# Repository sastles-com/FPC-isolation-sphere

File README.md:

# Isolation Sphere V2

直径 100 mm の球体 LED ディスプレイ。約 800 個の WS2812-2020 を  
**ゴールドバーグ多面体 T=81** の球面に配置した "デジタル地球儀" 風ピクセルディスプレイ。

**A 100 mm spherical LED display with ~800 WS2812-2020 pixels  
arranged on a Goldberg polyhedron (T=81) shell.**

---

## コンセプト / Concept

前作はスパイラル配線＋接着剤固定で LED 1 個の故障が全損につながる設計だった。  
V2 では **カセット交換式・接着剤ゼロ** に全面刷新する。

> V1 was glued together — a single dead LED bricked the sphere.  
> V2 makes every section a **hot-swappable cassette with zero adhesive**.

| 項目 | 仕様 |
|---|---|
| 外径 | φ100 mm |
| 多面体 | Goldberg G(9,0)、T=81 |
| LED | WS2812-2020 × **800 個** |
| 分割 | 経度 5 × 南北 2 = **10 カセット** |
| コントローラ | ESP32 系（6 並列 RMT/PIO 出力） |
| バッテリ | LiPo 2000 mAh × 2 |

---

## 現在のフェーズ / Current Phase

**概念設計 + 3D CAD スクリプト開発中**

- [x] Goldberg T=81 メッシュ生成（`goldberg.py`）
- [x] カセット分割・可視化（Blender Python）
- [x] ヘキサゴン錐 + 円柱アパーチャの Boolean 生成（`aperture_boolean_demo.py`）
- [ ] カセット外殻 STL 完成
- [ ] FPC（骨組み基板）KiCad 設計
- [ ] 極専用 Rigid PCB × 2
- [ ] 赤道マザーリング基板
- [ ] ファームウェア（ESP32）

---

## 3D ビューア / 3D Viewer

生成した STL を Lolipop サーバーで公開中：

| モデル | URL |
|---|---|
| 全球アパーチャ | http://tajmahal.mond.jp/isolation-sphere/web/output/aperture_demo_fullsphere_viewer.html |
| カセット 0 のみ | http://tajmahal.mond.jp/isolation-sphere/web/output/aperture_demo_cassette0_viewer.html |
| ヘキサゴン錐（面取りあり） | http://tajmahal.mond.jp/isolation-sphere/web/output/hex_pyramids_l5_b0.5_viewer.html |

---

## セットアップ / Setup

```bash
# Python 3.11 + uv が必要
uv sync
```

---

## スクリプト一覧 / Scripts

### `shell-cad/scripts/goldberg.py`
Goldberg G(m,0) 多面体ジェネレータ。T=81 メッシュを OBJ で出力。

```bash
uv run python shell-cad/scripts/goldberg.py        # T=81, r=50mm
uv run python shell-cad/scripts/goldberg.py -m 3   # T=9
```

### `shell-cad/scripts/hex_pyramids.py`
各ヘキサゴン面から LED アパーチャ用の六角錐を生成。OBJ / STL 出力。

```bash
uv run python shell-cad/scripts/hex_pyramids.py --l_h 5 --bevel 0.5 --base_r 52
```

| パラメータ | 説明 |
|---|---|
| `--l_h` | 錐の深さ mm |
| `--bevel` | 辺の面取り mm（0=シャープ） |
| `--base_r` | 底面を配置する半径 mm |

### `shell-cad/scripts/aperture_boolean_demo.py`
球殻から六角錐 + 円柱ボアを Boolean 差分で除去した STL を生成。  
スクリプト先頭のパラメータブロックで形状をチューニングできる。

```bash
uv run python shell-cad/scripts/aperture_boolean_demo.py            # 全球
uv run python shell-cad/scripts/aperture_boolean_demo.py --cassette 0  # 1カセットのみ
```

**チューニングパラメータ（スクリプト先頭）:**

```python
R_OUTER     = 52.0   # 外殻半径 mm
R_INNER     = 47.0   # 内殻半径 mm  (差 = 壁厚)
L_H         =  8.0   # 錐の深さ mm
BEVEL       =  0.0   # 面取り mm
CYL_R       =  1.2   # ボア半径 mm
CYL_ENABLE  = True   # False で円柱を無効化
SPHERE_SUBS =  5     # 球メッシュ細分割数
CYL_SECTS   = 16     # 円柱多角形分割数
```

### `shell-cad/scripts/generate_stl_viewer.py`
STL → Three.js インタラクティブ HTML ビューアを生成。

```bash
uv run python shell-cad/scripts/generate_stl_viewer.py shell-cad/output/foo.stl
```

### `shell-cad/scripts/upload_to_lolipop.sh`
`web/output/` 以下を Lolipop FTP サーバーへアップロード。  
認証情報は `.ftp_credentials`（gitignore 済）に記載。

```bash
bash shell-cad/scripts/upload_to_lolipop.sh           # 一括
bash shell-cad/scripts/upload_to_lolipop.sh path/to/file.html  # 単ファイル
```

---

## フォルダ構成 / Repository Layout

```text
.
├── CLAUDE.md                    Claude Code 用プロジェクトガイド
├── docs/
│   ├── 10pieces-isolation-sphere-concept.md  設計議論ログ（一次資料）
│   ├── 01-shell-cad.md          外殻 CAD 仕様
│   ├── 02-fpc-kicad.md          FPC / Rigid PCB 仕様
│   └── 03-power-charging.md     電源・充電仕様
├── shell-cad/
│   └── scripts/                 Python 生成スクリプト群
├── fpc-kicad/
│   └── legacy/                  V1 KiCad スクリプト（参照用）
├── shared/                      Blender ↔ KiCad 共有データ（LED座標 CSV）
└── web/output/                  生成 HTML + STL（gitignore）
```

---

## ライセンス / License

Private repository — Yasuo Katano

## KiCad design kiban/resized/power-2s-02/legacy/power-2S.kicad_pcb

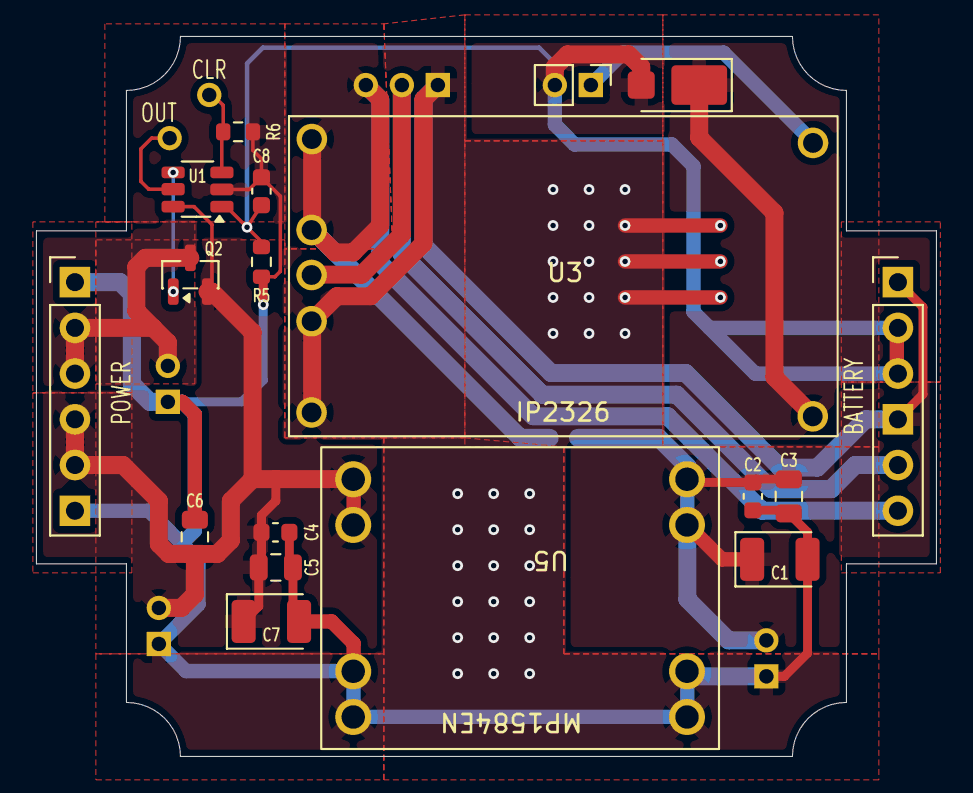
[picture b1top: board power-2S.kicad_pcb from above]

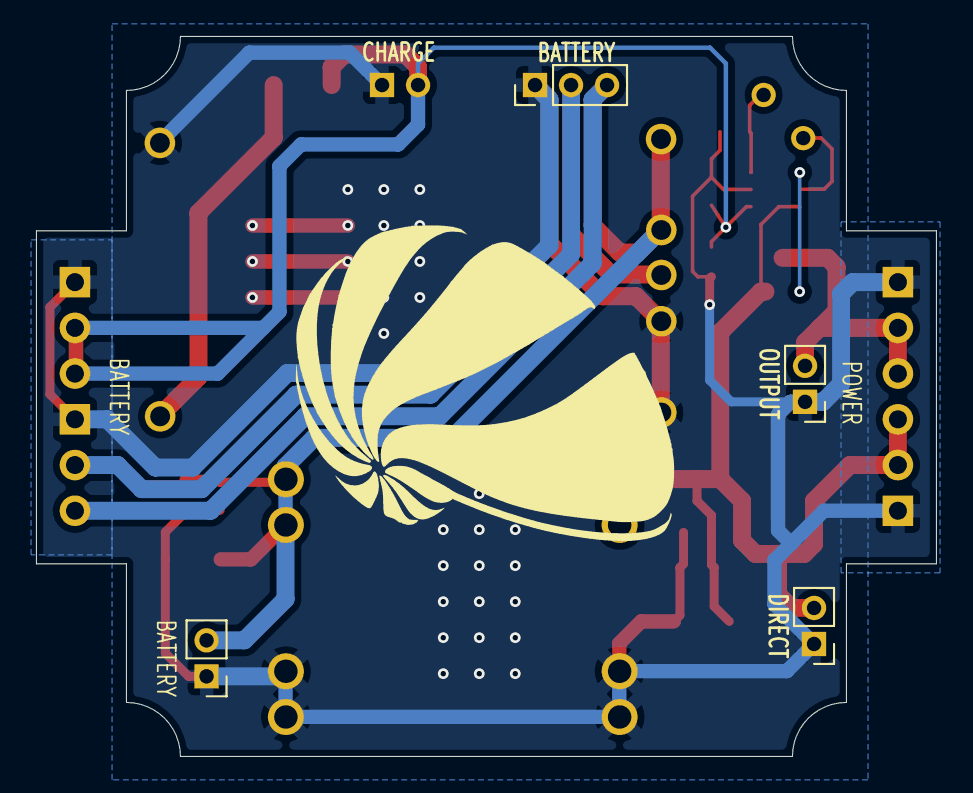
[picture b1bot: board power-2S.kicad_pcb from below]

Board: 2 copper layers, 50.0 x 40.0 mm, 25 parts (5 on the bottom side), 11 nets.

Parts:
C1, C7: 100uF; CP_EIA-3528-12_Kemet-T
C2, C4, C8: 0.1uF; C_0603_1608Metric
C3, C5, C6: 22uF; C_0805_2012Metric
D1: D_Schottky_Small; Vishay_SMPA
FB1: FerriteBead; L_0603_1608Metric
J1: BATTERY; PinHeader_1x03_P2.00mm_Vertical
J3: BATTERY; PinHeader_1x02_P2.00mm_Vertical
J4: DIRECT; PinHeader_1x02_P2.00mm_Vertical
J7: VOUT; PinHeader_1x06_P2.54mm_Vertical
J8: VIN; PinHeader_1x06_P2.54mm_Vertical
J9: OUTPUT; PinHeader_1x02_P2.00mm_Vertical
J11: OUT; PinHeader_1x01_P2.00mm_Vertical
J12: CLR; PinHeader_1x01_P2.00mm_Vertical
J14: CHARGE; PinHeader_1x02_P2.00mm_Vertical
Q2: DMG3415; SOT-23
R5: 47kΩ; R_0603_1608Metric
R6: 10kΩ; R_0603_1608Metric
U1: MAX16054; TSOT-23-6_HandSoldering
U3: IP2326; TS2326
U5: MP1584EN

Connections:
BM: J1.2, J8.5, U3.2 (BM)
CHARGE: D1.1 (K), U3.4 (VIN)
CLR: J12.1 (Pin_1_1), R6.2, U1.3 (CLR)
GATE: Q2.1 (G), U1.4 (OUT_)
OUT: J11.1 (Pin_1_1), U1.5 (OUT)
P+: FB1.1, J1.3, J8.6, U3.1 (B+)
PGND: C1.2, C2.2, C3.2, C4.2, C5.2, C6.2, C7.2, C8.2, J1.1, J3.1, J4.1, J7.1, J7.6, J8.1, J8.4, J9.1, J14.1, R5.2, R6.1, U1.2 (GND), U3.3 (B-), U3.5 (GND), U5.1 (IN-), U5.4 (OUT-)
POWER: C8.1, D1.2 (A), J8.2, J8.3, J14.2, R5.1, U1.1 (IN)
VIN: C1.1, C2.1, C3.1, FB1.2, J3.2, U5.2 (IN+)
VOUT: C4.1, C5.1, C6.1, C7.1, J4.2, J7.4, J7.5, Q2.2 (S), U1.6 (VCC), U5.3 (OUT+)
VOUT_SWITCHED: J7.2, J7.3, J9.2, Q2.3 (D)

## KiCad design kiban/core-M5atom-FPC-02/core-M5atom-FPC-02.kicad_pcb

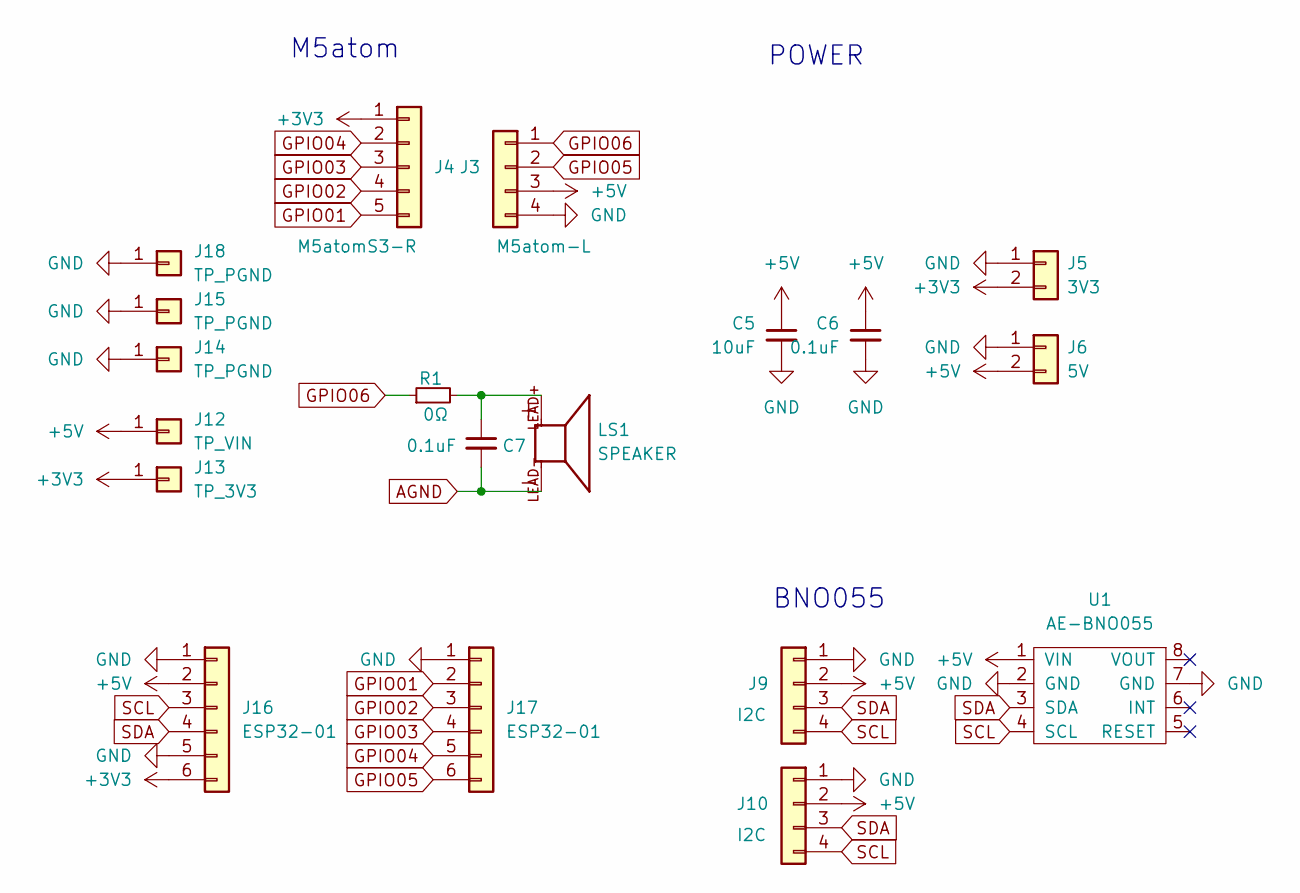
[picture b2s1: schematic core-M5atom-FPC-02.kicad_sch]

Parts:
C5: 10uF; C_0603_1608Metric_Pad1.08x0.95mm_HandSolder
C6, C7: 0.1uF; C_0603_1608Metric_Pad1.08x0.95mm_HandSolder
J3: M5atom-L; PinHeader_1x04_P2.54mm_Vertical_SMD_Pin1Left
J4: M5atomS3-R; PinHeader_1x05_P2.54mm_Vertical_SMD_Pin1Left
J5: 3V3; PinHeader_1x02_P2.00mm_Vertical
J6: 5V; PinHeader_1x02_P2.00mm_Vertical
J9, J10: I2C; PinHeader_1x04_P2.00mm_Vertical
J12: TP_VIN; PinHeader_1x01_P2.54mm_Vertical
J13: TP_3V3; PinHeader_1x01_P2.54mm_Vertical
J14, J15, J18: TP_PGND; PinHeader_1x01_P2.54mm_Vertical
J16, J17: ESP32-01; PinHeader_1x06_P2.54mm_Vertical
LS1: SPEAKER; speaker-PKLCS1212; PARTREV C
R1: 0Ω; C_0603_1608Metric
U1: AE-BNO055; AE-BNO055-nohole

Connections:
+3V3: J4.1, J5.2, J13.1 (Pin_1_1), J16.6
+5V: C5.1, C6.1, J3.3, J6.2, J9.2, J10.2, J12.1 (Pin_1_1), J16.2, U1.1 (VIN)
AGND: C7.2, LS1.LEAD-
GND: C5.2, C6.2, J3.4, J5.1, J6.1, J9.1, J10.1, J14.1 (Pin_1_1), J15.1 (Pin_1_1), J16.1, J16.5, J17.1, J18.1 (Pin_1_1), U1.2 (GND), U1.7 (GND)
GPIO01: J4.5, J17.2
GPIO02: J4.4, J17.3
GPIO03: J4.3, J17.4
GPIO04: J4.2, J17.5
GPIO05: J3.2, J17.6
GPIO06: J3.1, R1.1
unnamed: C7.1, LS1.LEAD+, R1.2
SCL: J9.4, J10.4, J16.3, U1.4 (SCL)
SDA: J9.3, J10.3, J16.4, U1.3 (SDA)

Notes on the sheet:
M5atom
BNO055
POWER

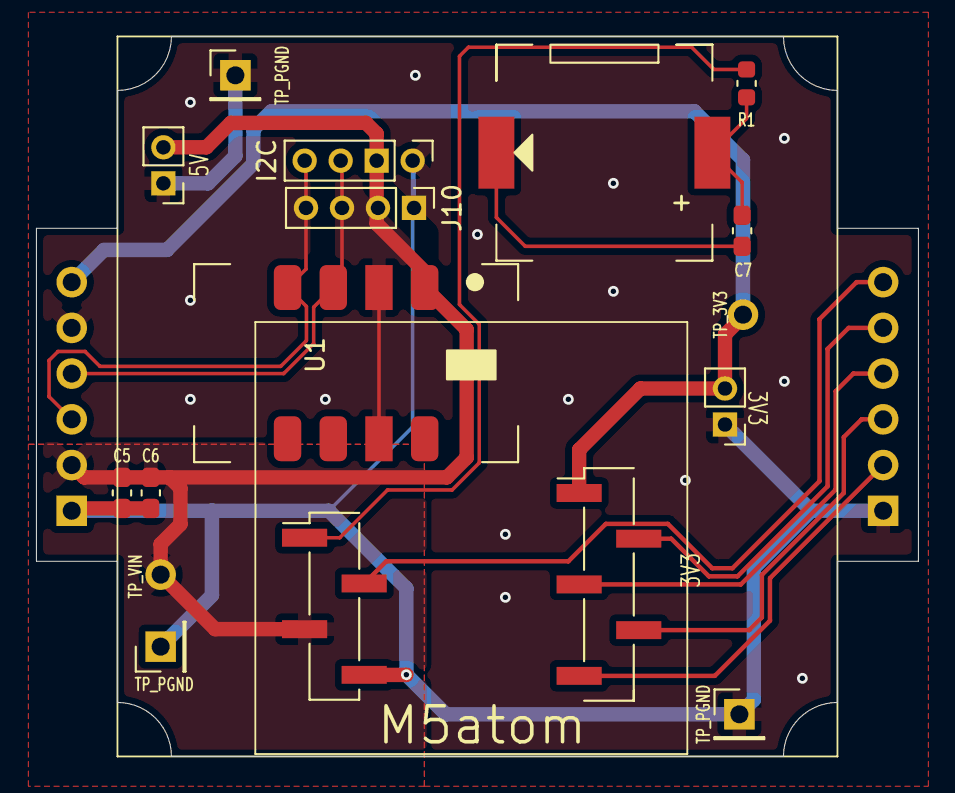
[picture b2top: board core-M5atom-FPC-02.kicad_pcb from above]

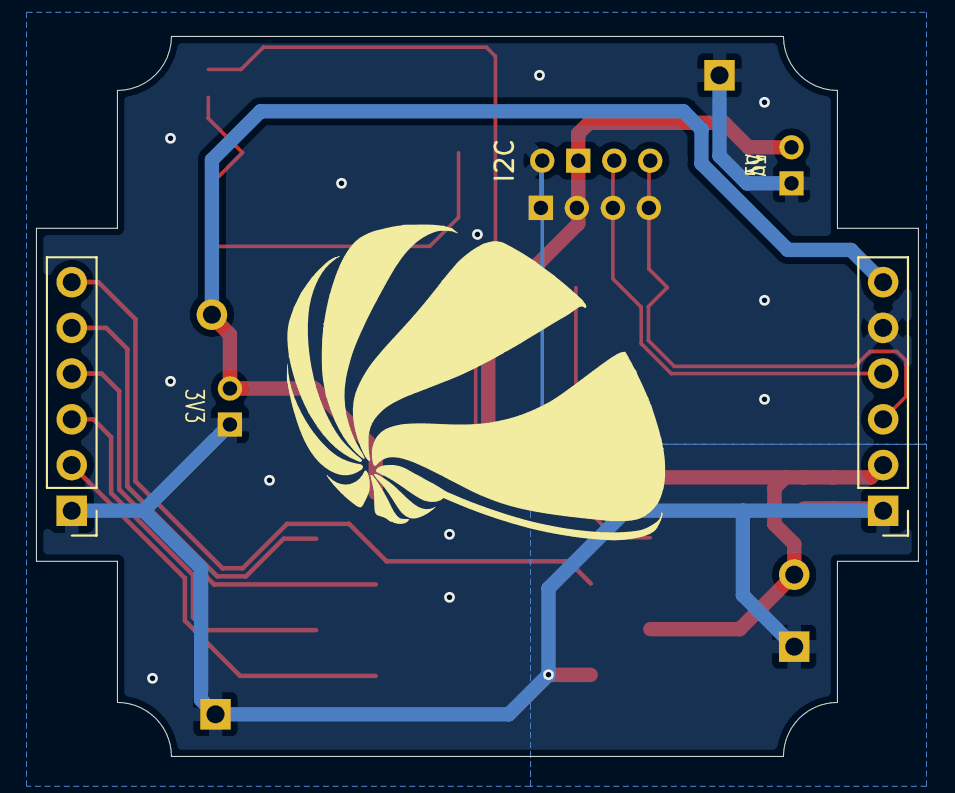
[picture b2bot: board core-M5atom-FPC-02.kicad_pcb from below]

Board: 2 copper layers, 49.0 x 40.0 mm, 19 parts (2 on the bottom side), 13 nets.

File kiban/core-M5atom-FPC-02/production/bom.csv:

Designator,Footprint,Quantity,Value,LCSC Part #
C5,0603,1,10uF,
"C6, C7",0603,2,0.1uF,
J12,PinHeader_1x01_P2.54mm_Vertical,1,TP_VIN,
J13,PinHeader_1x01_P2.54mm_Vertical,1,TP_3V3,
"J14, J15, J18",PinHeader_1x01_P2.54mm_Vertical,3,TP_PGND,
"J16, J17",PinHeader_1x06_P2.54mm_Vertical,2,ESP32-01,
J3,PinHeader_1x04_P2.54mm_Vertical_SMD_Pin1Left,1,M5atom-L,
J4,PinHeader_1x05_P2.54mm_Vertical_SMD_Pin1Left,1,M5atomS3-R,
J5,PinHeader_1x02_P2.00mm_Vertical,1,3V3,
J6,PinHeader_1x02_P2.00mm_Vertical,1,5V,
J9,PinHeader_1x04_P2.00mm_Vertical,1,I2C,
LS1,speaker-PKLCS1212,1,SPEAKER,
R1,0603,1,0Ω,
U1,AE-BNO055-nohole,1,AE-BNO055,

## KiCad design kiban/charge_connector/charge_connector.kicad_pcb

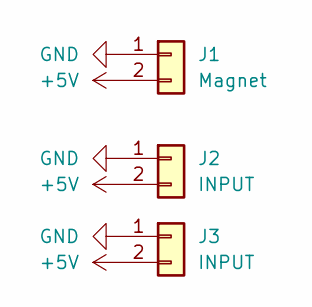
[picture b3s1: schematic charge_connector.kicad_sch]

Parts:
J1: Magnet; magnet_contact
J2: INPUT; PinHeader_1x02_P2.00mm_Vertical
J3: INPUT; PinHeader_1x02_P2.54mm_Vertical

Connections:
+5V: J1.2, J2.2, J3.2
GND: J1.1, J2.1, J3.1

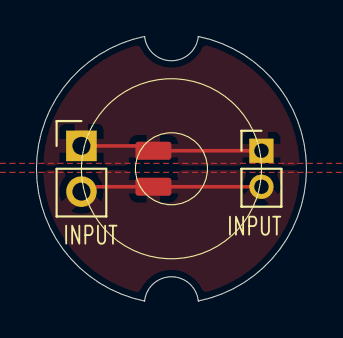
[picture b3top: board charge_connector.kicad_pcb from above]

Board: 2 copper layers, 15.0 x 14.7 mm, 3 parts (0 on the bottom side), 2 nets.

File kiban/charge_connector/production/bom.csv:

Designator,Footprint,Quantity,Value,LCSC Part #
J1,magnet_contact,1,Magnet,
J2,PinHeader_1x02_P2.00mm_Vertical,1,INPUT,
J3,PinHeader_1x02_P2.54mm_Vertical,1,INPUT,

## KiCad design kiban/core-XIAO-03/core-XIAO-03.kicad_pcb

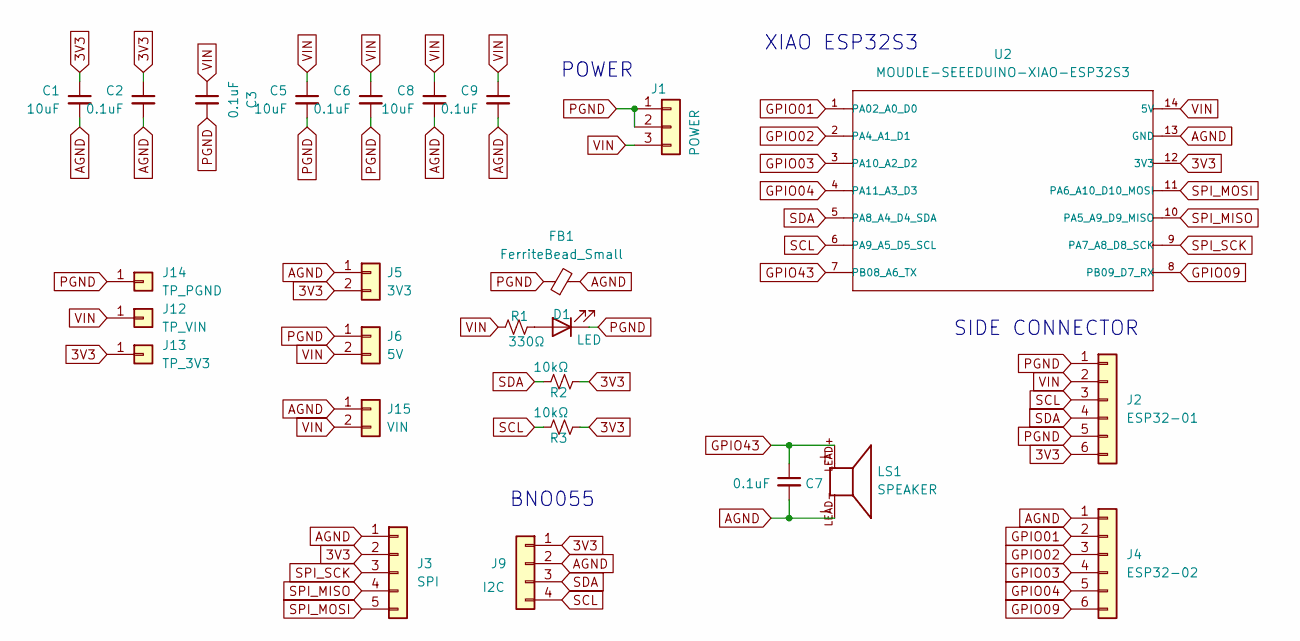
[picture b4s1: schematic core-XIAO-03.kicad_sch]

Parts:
C1, C5, C8: 10uF; C_0603_1608Metric_Pad1.08x0.95mm_HandSolder
C2, C3, C6, C7, C9: 0.1uF; C_0603_1608Metric_Pad1.08x0.95mm_HandSolder
D1: LED; LED_0603_1608Metric
FB1: FerriteBead_Small; C_0603_1608Metric_Pad1.08x0.95mm_HandSolder
J1: POWER; PinHeader_1x03_P2.00mm_Vertical
J2: ESP32-01; PinHeader_1x06_P2.54mm_Vertical
J3: SPI; PinHeader_1x05_P2.00mm_Vertical
J4: ESP32-02; PinHeader_1x06_P2.54mm_Vertical
J5: 3V3; PinHeader_1x02_P2.00mm_Vertical
J6: 5V; PinHeader_1x02_P2.00mm_Vertical
J9: I2C; PinHeader_1x04_P2.54mm_Vertical
J12: TP_VIN; PinHeader_1x01_P2.54mm_Vertical
J13: TP_3V3; PinHeader_1x01_P2.54mm_Vertical
J14: TP_PGND; PinHeader_1x01_P2.54mm_Vertical
J15: VIN; PinHeader_1x02_P2.00mm_Vertical
LS1: SPEAKER; speaker-PKLCS1212; PARTREV C
R1: 330Ω; R_0603_1608Metric
R2, R3: 10kΩ; R_0603_1608Metric
U2: MOUDLE-SEEEDUINO-XIAO-ESP32S3; XIAO-RP2350

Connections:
3V3: C1.1, C2.1, J2.6, J3.2, J5.2, J9.1, J13.1 (Pin_1_1), R2.1, R3.1, U2.12 (3V3)
AGND: C1.2, C2.2, C7.2, C8.2, C9.2, FB1.2, J3.1, J4.1, J5.1, J9.2, J15.1, LS1.LEAD-, U2.13 (GND)
GPIO01: J4.2, U2.1 (PA02_A0_D0)
GPIO02: J4.3, U2.2 (PA4_A1_D1)
GPIO03: J4.4, U2.3 (PA10_A2_D2)
GPIO04: J4.5, U2.4 (PA11_A3_D3)
GPIO09: J4.6, U2.8 (PB09_D7_RX)
GPIO43: C7.1, LS1.LEAD+, U2.7 (PB08_A6_TX)
unnamed: D1.2 (A), R1.2
PGND: C3.2, C5.2, C6.2, D1.1 (K), FB1.1, J1.1, J1.2, J2.1, J2.5, J6.1, J14.1 (Pin_1_1); also elsewhere on the board
SCL: J2.3, J9.4, R3.2, U2.6 (PA9_A5_D5_SCL)
SDA: J2.4, J9.3, R2.2, U2.5 (PA8_A4_D4_SDA)
SPI_MISO: J3.4, U2.10 (PA5_A9_D9_MISO)
SPI_MOSI: J3.5, U2.11 (PA6_A10_D10_MOSI)
SPI_SCK: J3.3, U2.9 (PA7_A8_D8_SCK)
VIN: C3.1, C5.1, C6.1, C8.1, C9.1, J1.3, J2.2, J6.2, J12.1 (Pin_1_1), J15.2, R1.1, U2.14 (5V)

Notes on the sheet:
XIAO ESP32S3
SIDE CONNECTOR
BNO055
POWER

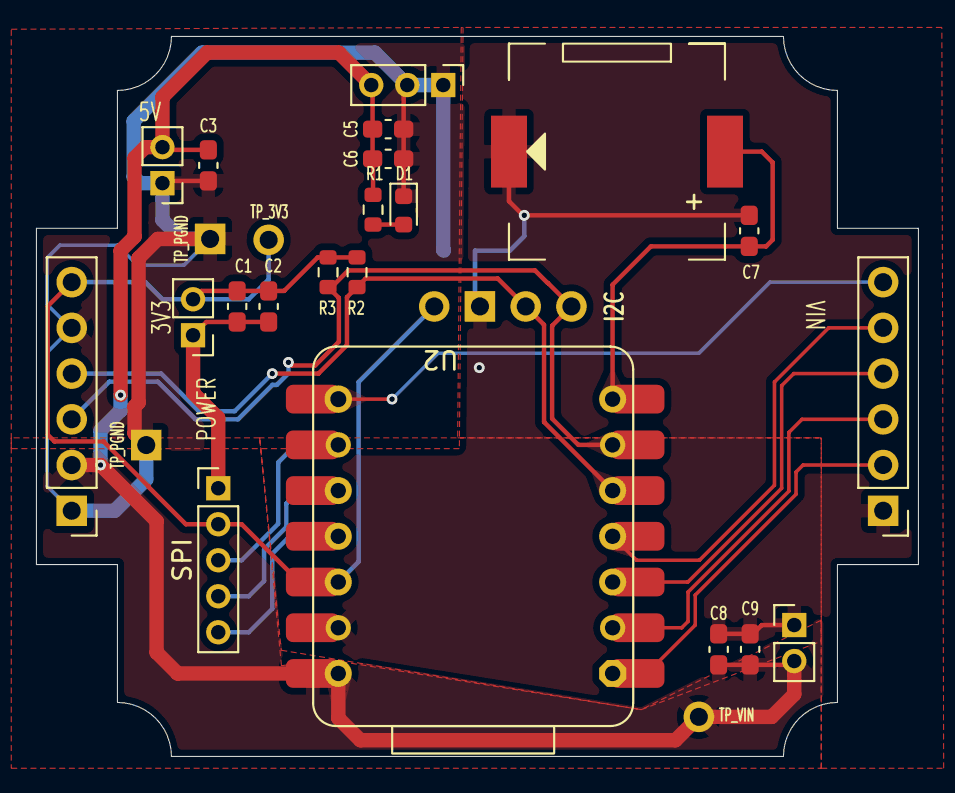
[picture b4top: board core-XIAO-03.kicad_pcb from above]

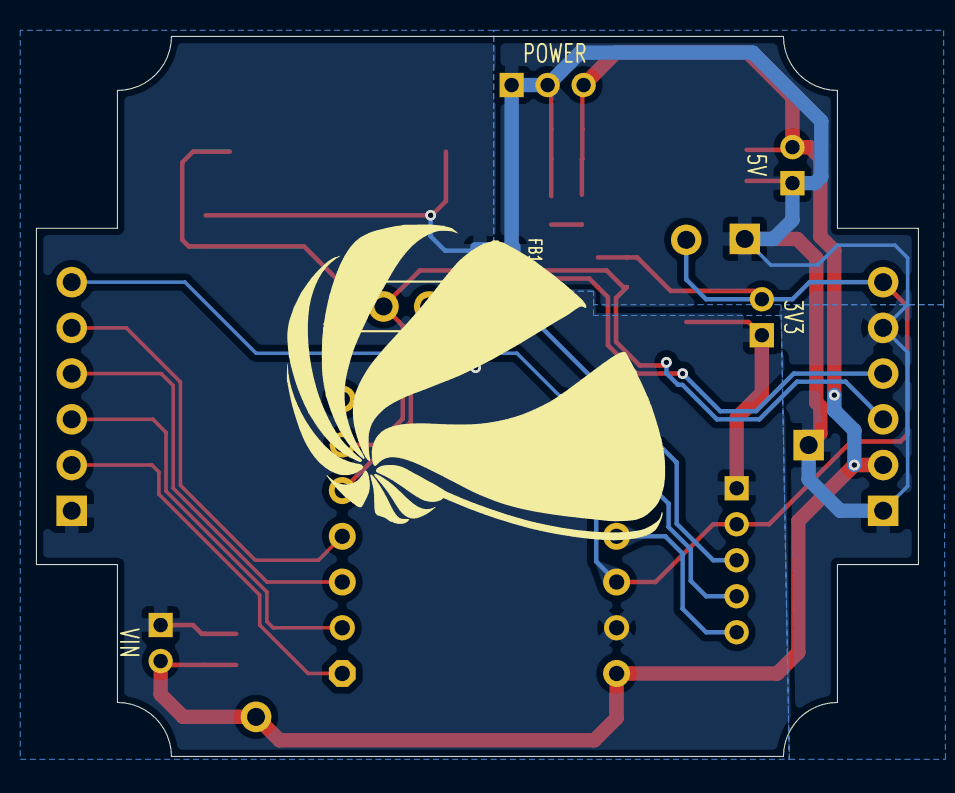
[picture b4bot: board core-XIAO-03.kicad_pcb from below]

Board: 2 copper layers, 49.0 x 40.0 mm, 27 parts (2 on the bottom side), 16 nets.

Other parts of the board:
J14#2: TP_PGND; PinHeader_1x01_P2.54mm_Vertical

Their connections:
PGND: J14#2.1 (Pin_1_1); also elsewhere on the board

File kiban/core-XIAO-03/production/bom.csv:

Designator,Footprint,Quantity,Value,LCSC Part #
"C1, C5, C8",0603,3,10uF,
"C2, C3, C6, C7, C9",0603,5,0.1uF,
D1,0603,1,LED,
FB1,0603,1,FerriteBead_Small,
J1,PinHeader_1x03_P2.00mm_Vertical,1,POWER,
J12,PinHeader_1x01_P2.54mm_Vertical,1,TP_VIN,
J13,PinHeader_1x01_P2.54mm_Vertical,1,TP_3V3,
"J14_2, J14",PinHeader_1x01_P2.54mm_Vertical,2,TP_PGND,
J15,PinHeader_1x02_P2.00mm_Vertical,1,VIN,
J2,PinHeader_1x06_P2.54mm_Vertical,1,ESP32-01,
J3,PinHeader_1x05_P2.00mm_Vertical,1,SPI,
J4,PinHeader_1x06_P2.54mm_Vertical,1,ESP32-02,
J5,PinHeader_1x02_P2.00mm_Vertical,1,3V3,
J6,PinHeader_1x02_P2.00mm_Vertical,1,5V,
J9,PinHeader_1x04_P2.54mm_Vertical,1,I2C,
LS1,speaker-PKLCS1212,1,SPEAKER,
R1,0603,1,330Ω,
"R2, R3",0603,2,10kΩ,
U2,XIAO-RP2350,1,MOUDLE-SEEEDUINO-XIAO-ESP32S3,

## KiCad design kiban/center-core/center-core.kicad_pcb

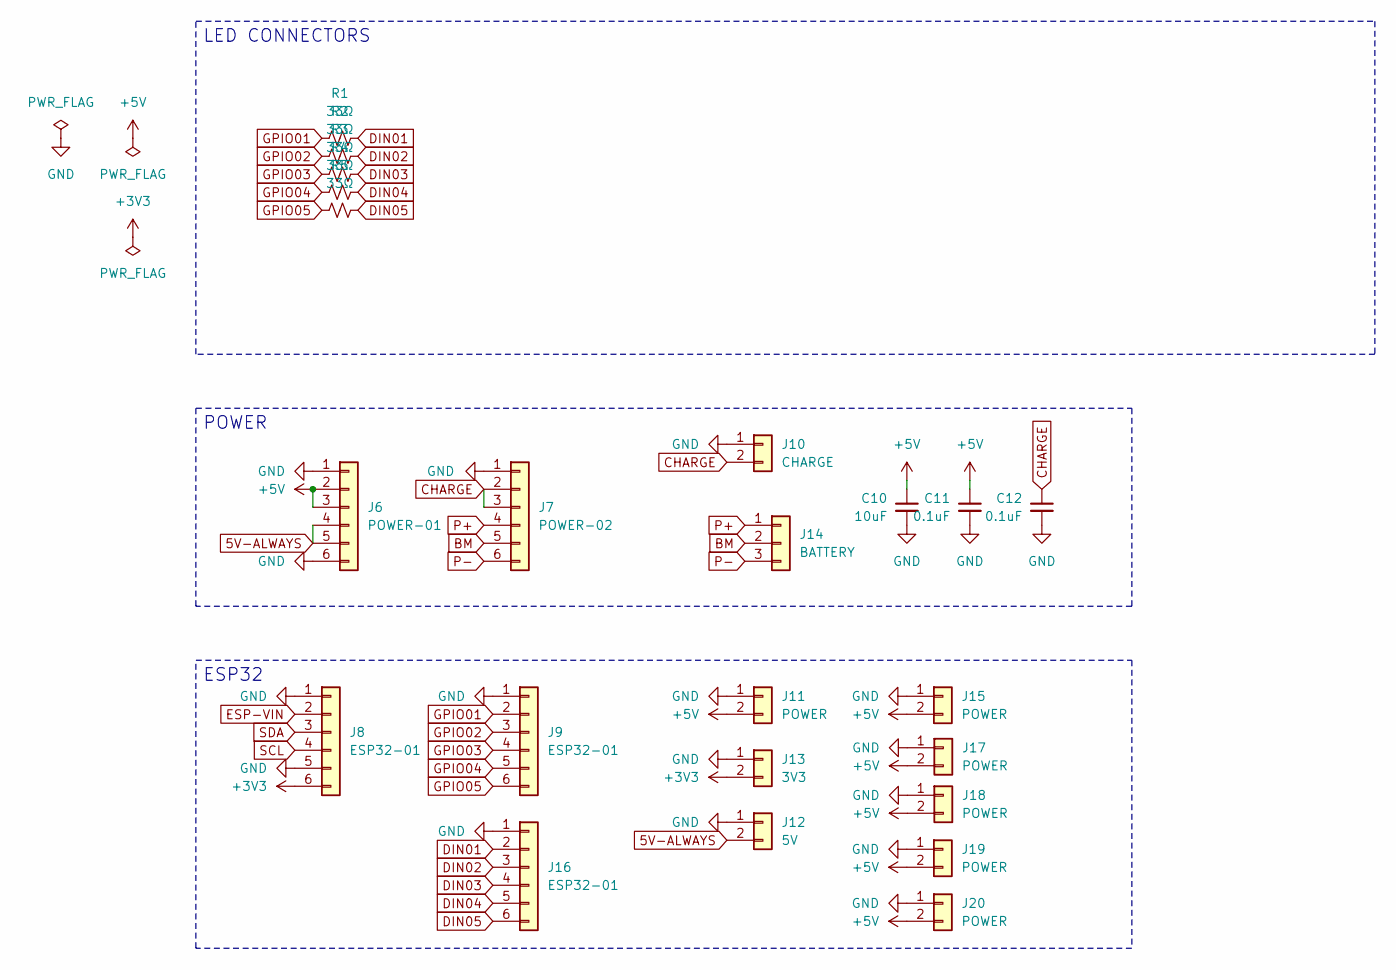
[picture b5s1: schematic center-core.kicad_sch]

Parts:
C10: 10uF; C_0603_1608Metric_Pad1.08x0.95mm_HandSolder
C11, C12: 0.1uF; C_0603_1608Metric_Pad1.08x0.95mm_HandSolder
J6: POWER-01; PinHeader_1x06_P2.54mm_Vertical
J7: POWER-02; PinHeader_1x06_P2.54mm_Vertical
J8, J9, J16: ESP32-01; PinHeader_1x06_P2.54mm_Vertical
J10: CHARGE; PinHeader_1x02_P2.00mm_Vertical
J11, J15, J17, J18, J19, J20: POWER; PinHeader_1x02_P2.00mm_Vertical
J12: 5V; PinHeader_1x02_P2.00mm_Vertical
J13: 3V3; PinHeader_1x02_P2.00mm_Vertical
J14: BATTERY; PinHeader_1x03_P2.00mm_Vertical
R1, R2, R3, R4, R5: 33Ω; R_0603_1608Metric

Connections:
5V-ALWAYS: J6.4, J6.5, J12.2
+3V3: J8.6, J13.2
+5V: C10.1, C11.1, J6.2, J6.3, J11.2, J15.2, J17.2, J18.2, J19.2, J20.2
BM: J7.5, J14.2
CHARGE: C12.1, J7.2, J7.3, J10.2
DIN01: J16.2, R1.2
DIN02: J16.3, R2.2
DIN03: J16.4, R3.2
DIN04: J16.5, R4.2
DIN05: J16.6, R5.2
ESP-VIN: J8.2
GND: C10.2, C11.2, C12.2, J6.1, J6.6, J7.1, J8.1, J8.5, J9.1, J10.1, J11.1, J12.1, J13.1, J15.1, J16.1, J17.1, J18.1, J19.1, J20.1
GPIO01: J9.2, R1.1
GPIO02: J9.3, R2.1
GPIO03: J9.4, R3.1
GPIO04: J9.5, R4.1
GPIO05: J9.6, R5.1
P+: J7.4, J14.1
P-: J7.6, J14.3
SCL: J8.4
SDA: J8.3

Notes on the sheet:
POWER
ESP32
LED CONNECTORS

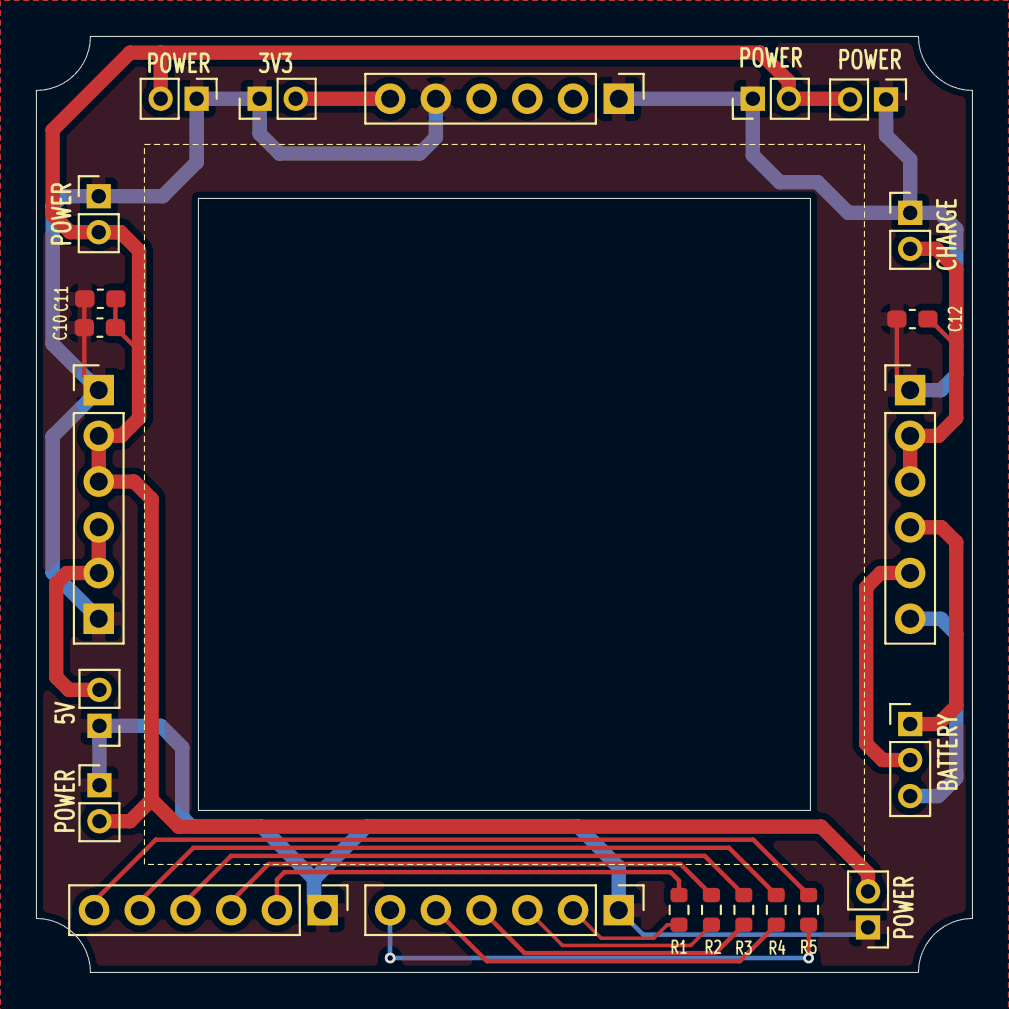
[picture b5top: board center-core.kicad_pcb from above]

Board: 2 copper layers, 52.0 x 52.0 mm, 23 parts (0 on the bottom side), 18 nets.

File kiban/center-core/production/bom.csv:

Designator,Footprint,Quantity,Value,LCSC Part #
C10,0603,1,10uF,
"C11, C12",0603,2,0.1uF,
J10,PinHeader_1x02_P2.00mm_Vertical,1,CHARGE,
"J11, J15, J17, J18, J19, J20",PinHeader_1x02_P2.00mm_Vertical,6,POWER,
J12,PinHeader_1x02_P2.00mm_Vertical,1,5V,
J13,PinHeader_1x02_P2.00mm_Vertical,1,3V3,
J14,PinHeader_1x03_P2.00mm_Vertical,1,BATTERY,
"J16, J8, J9",PinHeader_1x06_P2.54mm_Vertical,3,ESP32-01,
J6,PinHeader_1x06_P2.54mm_Vertical,1,POWER-01,
J7,PinHeader_1x06_P2.54mm_Vertical,1,POWER-02,
"R1, R2, R3, R4, R5",0603,5,33Ω,

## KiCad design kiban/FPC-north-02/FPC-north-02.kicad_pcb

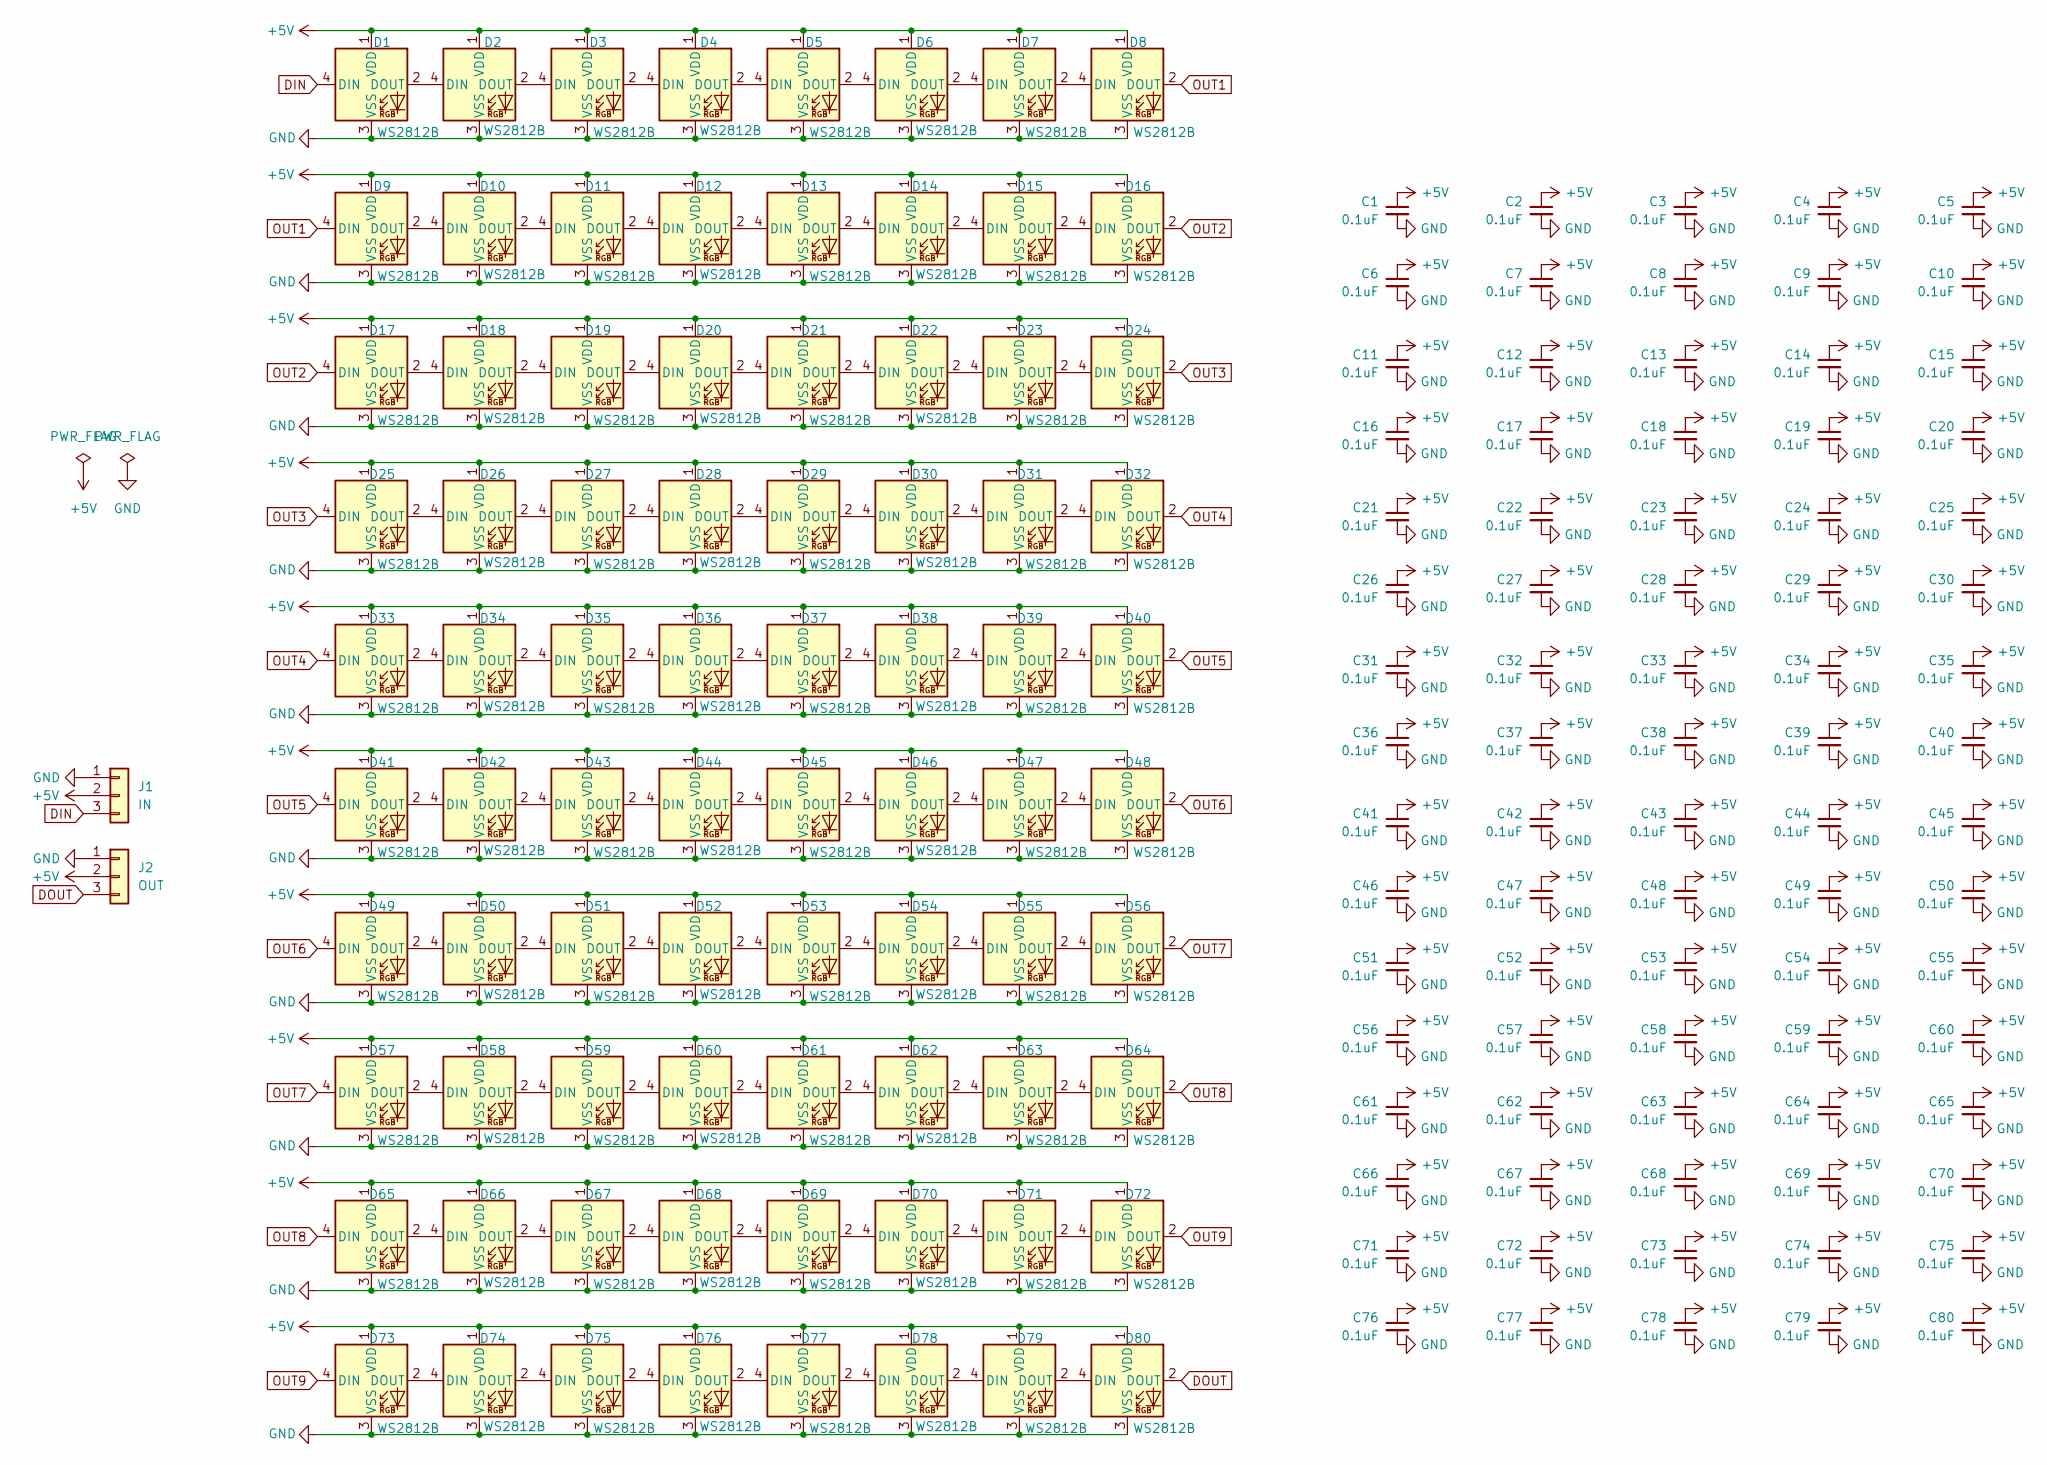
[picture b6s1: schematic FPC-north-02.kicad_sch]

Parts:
C1, C2, C3, C4, C5, C6, C7, C8, C9, C10, C11, C12, C13, C14, C15, C16, C17, C18, C19, C20, C21, C22, C23, C24, C25, C26, C27, C28, C29, C30, C31, C32, C33, C34, C35, C36, C37, C38, C39, C40, C41, C42, C43, C44, C45, C46, C47, C48, C49, C50, C51, C52, C53, C54, C55, C56, C57, C58, C59, C60, C61, C62, C63, C64, C65, C66, C67, C68, C69, C70, C71, C72, C73, C74, C75, C76, C77, C78, C79, C80: 0.1uF; C_0603_1608Metric
D1, D2, D3, D4, D5, D6, D7, D8, D9, D10, D11, D12, D13, D14, D15, D16, D17, D18, D19, D20, D21, D22, D23, D24, D25, D26, D27, D28, D29, D30, D31, D32, D33, D34, D35, D36, D37, D38, D39, D40, D41, D42, D43, D44, D45, D46, D47, D48, D49, D50, D51, D52, D53, D54, D55, D56, D57, D58, D59, D60, D61, D62, D63, D64, D65, D66, D67, D68, D69, D70, D71, D72, D73, D74, D75, D76, D77, D78, D79, D80: WS2812B; WS2812C-2020-nocut
J1: IN; PinHeader_1x03_P2.00mm_Vertical
J2: OUT; PinHeader_1x03_P2.00mm_Vertical

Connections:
+5V: C1.1, C2.1, C3.1, C4.1, C5.1, C6.1, C7.1, C8.1, C9.1, C10.1, C11.1, C12.1, C13.1, C14.1, C15.1, C16.1, C17.1, C18.1, C19.1, C20.1, C21.1, C22.1, C23.1, C24.1, C25.1, C26.1, C27.1, C28.1, C29.1, C30.1, C31.1, C32.1, C33.1, C34.1, C35.1, C36.1, C37.1, C38.1, C39.1, C40.1, C41.1, C42.1, C43.1, C44.1, C45.1, C46.1, C47.1, C48.1, C49.1, C50.1, C51.1, C52.1, C53.1, C54.1, C55.1, C56.1, C57.1, C58.1, C59.1, C60.1, C61.1, C62.1, C63.1, C64.1, C65.1, C66.1, C67.1, C68.1, C69.1, C70.1, C71.1, C72.1, C73.1, C74.1, C75.1, C76.1, C77.1, C78.1, C79.1, C80.1, D1.1 (VDD), D2.1 (VDD), D3.1 (VDD), D4.1 (VDD), D5.1 (VDD), D6.1 (VDD), D7.1 (VDD), D8.1 (VDD), D9.1 (VDD), D10.1 (VDD), D11.1 (VDD), D12.1 (VDD), D13.1 (VDD), D14.1 (VDD), D15.1 (VDD), D16.1 (VDD), D17.1 (VDD), D18.1 (VDD), D19.1 (VDD), D20.1 (VDD), D21.1 (VDD), D22.1 (VDD), D23.1 (VDD), D24.1 (VDD), D25.1 (VDD), D26.1 (VDD), D27.1 (VDD), D28.1 (VDD), D29.1 (VDD), D30.1 (VDD), D31.1 (VDD), D32.1 (VDD), D33.1 (VDD), D34.1 (VDD), D35.1 (VDD), D36.1 (VDD), D37.1 (VDD), D38.1 (VDD), D39.1 (VDD), D40.1 (VDD), D41.1 (VDD), D42.1 (VDD), D43.1 (VDD), D44.1 (VDD), D45.1 (VDD), D46.1 (VDD), D47.1 (VDD), D48.1 (VDD), D49.1 (VDD), D50.1 (VDD), D51.1 (VDD), D52.1 (VDD), D53.1 (VDD), D54.1 (VDD), D55.1 (VDD), D56.1 (VDD), D57.1 (VDD), D58.1 (VDD), D59.1 (VDD), D60.1 (VDD), D61.1 (VDD), D62.1 (VDD), D63.1 (VDD), D64.1 (VDD), D65.1 (VDD), D66.1 (VDD), D67.1 (VDD), D68.1 (VDD), D69.1 (VDD), D70.1 (VDD), D71.1 (VDD), D72.1 (VDD), D73.1 (VDD), D74.1 (VDD), D75.1 (VDD), D76.1 (VDD), D77.1 (VDD), D78.1 (VDD), D79.1 (VDD), D80.1 (VDD), J1.2, J2.2
DIN: D1.4 (DIN), J1.3
DOUT: D80.2 (DOUT), J2.3
GND: C1.2, C2.2, C3.2, C4.2, C5.2, C6.2, C7.2, C8.2, C9.2, C10.2, C11.2, C12.2, C13.2, C14.2, C15.2, C16.2, C17.2, C18.2, C19.2, C20.2, C21.2, C22.2, C23.2, C24.2, C25.2, C26.2, C27.2, C28.2, C29.2, C30.2, C31.2, C32.2, C33.2, C34.2, C35.2, C36.2, C37.2, C38.2, C39.2, C40.2, C41.2, C42.2, C43.2, C44.2, C45.2, C46.2, C47.2, C48.2, C49.2, C50.2, C51.2, C52.2, C53.2, C54.2, C55.2, C56.2, C57.2, C58.2, C59.2, C60.2, C61.2, C62.2, C63.2, C64.2, C65.2, C66.2, C67.2, C68.2, C69.2, C70.2, C71.2, C72.2, C73.2, C74.2, C75.2, C76.2, C77.2, C78.2, C79.2, C80.2, D1.3 (VSS), D2.3 (VSS), D3.3 (VSS), D4.3 (VSS), D5.3 (VSS), D6.3 (VSS), D7.3 (VSS), D8.3 (VSS), D9.3 (VSS), D10.3 (VSS), D11.3 (VSS), D12.3 (VSS), D13.3 (VSS), D14.3 (VSS), D15.3 (VSS), D16.3 (VSS), D17.3 (VSS), D18.3 (VSS), D19.3 (VSS), D20.3 (VSS), D21.3 (VSS), D22.3 (VSS), D23.3 (VSS), D24.3 (VSS), D25.3 (VSS), D26.3 (VSS), D27.3 (VSS), D28.3 (VSS), D29.3 (VSS), D30.3 (VSS), D31.3 (VSS), D32.3 (VSS), D33.3 (VSS), D34.3 (VSS), D35.3 (VSS), D36.3 (VSS), D37.3 (VSS), D38.3 (VSS), D39.3 (VSS), D40.3 (VSS), D41.3 (VSS), D42.3 (VSS), D43.3 (VSS), D44.3 (VSS), D45.3 (VSS), D46.3 (VSS), D47.3 (VSS), D48.3 (VSS), D49.3 (VSS), D50.3 (VSS), D51.3 (VSS), D52.3 (VSS), D53.3 (VSS), D54.3 (VSS), D55.3 (VSS), D56.3 (VSS), D57.3 (VSS), D58.3 (VSS), D59.3 (VSS), D60.3 (VSS), D61.3 (VSS), D62.3 (VSS), D63.3 (VSS), D64.3 (VSS), D65.3 (VSS), D66.3 (VSS), D67.3 (VSS), D68.3 (VSS), D69.3 (VSS), D70.3 (VSS), D71.3 (VSS), D72.3 (VSS), D73.3 (VSS), D74.3 (VSS), D75.3 (VSS), D76.3 (VSS), D77.3 (VSS), D78.3 (VSS), D79.3 (VSS), D80.3 (VSS), J1.1, J2.1
unnamed: D1.2 (DOUT), D2.4 (DIN)
unnamed: D2.2 (DOUT), D3.4 (DIN)
unnamed: D3.2 (DOUT), D4.4 (DIN)
unnamed: D4.2 (DOUT), D5.4 (DIN)
unnamed: D5.2 (DOUT), D6.4 (DIN)
unnamed: D6.2 (DOUT), D7.4 (DIN)
unnamed: D7.2 (DOUT), D8.4 (DIN)
unnamed: D9.2 (DOUT), D10.4 (DIN)
unnamed: D10.2 (DOUT), D11.4 (DIN)
unnamed: D11.2 (DOUT), D12.4 (DIN)
unnamed: D12.2 (DOUT), D13.4 (DIN)
unnamed: D13.2 (DOUT), D14.4 (DIN)
unnamed: D14.2 (DOUT), D15.4 (DIN)
unnamed: D15.2 (DOUT), D16.4 (DIN)
unnamed: D17.2 (DOUT), D18.4 (DIN)
unnamed: D18.2 (DOUT), D19.4 (DIN)
unnamed: D19.2 (DOUT), D20.4 (DIN)
unnamed: D20.2 (DOUT), D21.4 (DIN)
unnamed: D21.2 (DOUT), D22.4 (DIN)
unnamed: D22.2 (DOUT), D23.4 (DIN)
unnamed: D23.2 (DOUT), D24.4 (DIN)
unnamed: D25.2 (DOUT), D26.4 (DIN)
unnamed: D26.2 (DOUT), D27.4 (DIN)
unnamed: D27.2 (DOUT), D28.4 (DIN)
unnamed: D28.2 (DOUT), D29.4 (DIN)
unnamed: D29.2 (DOUT), D30.4 (DIN)
unnamed: D30.2 (DOUT), D31.4 (DIN)
unnamed: D31.2 (DOUT), D32.4 (DIN)
unnamed: D33.2 (DOUT), D34.4 (DIN)
unnamed: D34.2 (DOUT), D35.4 (DIN)
unnamed: D35.2 (DOUT), D36.4 (DIN)
unnamed: D36.2 (DOUT), D37.4 (DIN)
unnamed: D37.2 (DOUT), D38.4 (DIN)
unnamed: D38.2 (DOUT), D39.4 (DIN)
unnamed: D39.2 (DOUT), D40.4 (DIN)
unnamed: D41.2 (DOUT), D42.4 (DIN)
unnamed: D42.2 (DOUT), D43.4 (DIN)
unnamed: D43.2 (DOUT), D44.4 (DIN)
unnamed: D44.2 (DOUT), D45.4 (DIN)
unnamed: D45.2 (DOUT), D46.4 (DIN)
unnamed: D46.2 (DOUT), D47.4 (DIN)
unnamed: D47.2 (DOUT), D48.4 (DIN)
unnamed: D49.2 (DOUT), D50.4 (DIN)
unnamed: D50.2 (DOUT), D51.4 (DIN)
unnamed: D51.2 (DOUT), D52.4 (DIN)
unnamed: D52.2 (DOUT), D53.4 (DIN)
unnamed: D53.2 (DOUT), D54.4 (DIN)
unnamed: D54.2 (DOUT), D55.4 (DIN)
unnamed: D55.2 (DOUT), D56.4 (DIN)
unnamed: D57.2 (DOUT), D58.4 (DIN)
unnamed: D58.2 (DOUT), D59.4 (DIN)
unnamed: D59.2 (DOUT), D60.4 (DIN)
unnamed: D60.2 (DOUT), D61.4 (DIN)
unnamed: D61.2 (DOUT), D62.4 (DIN)
unnamed: D62.2 (DOUT), D63.4 (DIN)
unnamed: D63.2 (DOUT), D64.4 (DIN)
unnamed: D65.2 (DOUT), D66.4 (DIN)
unnamed: D66.2 (DOUT), D67.4 (DIN)
unnamed: D67.2 (DOUT), D68.4 (DIN)
unnamed: D68.2 (DOUT), D69.4 (DIN)
unnamed: D69.2 (DOUT), D70.4 (DIN)
unnamed: D70.2 (DOUT), D71.4 (DIN)
unnamed: D71.2 (DOUT), D72.4 (DIN)
unnamed: D73.2 (DOUT), D74.4 (DIN)
unnamed: D74.2 (DOUT), D75.4 (DIN)
unnamed: D75.2 (DOUT), D76.4 (DIN)
unnamed: D76.2 (DOUT), D77.4 (DIN)
unnamed: D77.2 (DOUT), D78.4 (DIN)
unnamed: D78.2 (DOUT), D79.4 (DIN)
unnamed: D79.2 (DOUT), D80.4 (DIN)
OUT1: D8.2 (DOUT), D9.4 (DIN)
OUT2: D16.2 (DOUT), D17.4 (DIN)
OUT3: D24.2 (DOUT), D25.4 (DIN)
OUT4: D32.2 (DOUT), D33.4 (DIN)
OUT5: D40.2 (DOUT), D41.4 (DIN)
OUT6: D48.2 (DOUT), D49.4 (DIN)
OUT7: D56.2 (DOUT), D57.4 (DIN)
OUT8: D64.2 (DOUT), D65.4 (DIN)
OUT9: D72.2 (DOUT), D73.4 (DIN)
